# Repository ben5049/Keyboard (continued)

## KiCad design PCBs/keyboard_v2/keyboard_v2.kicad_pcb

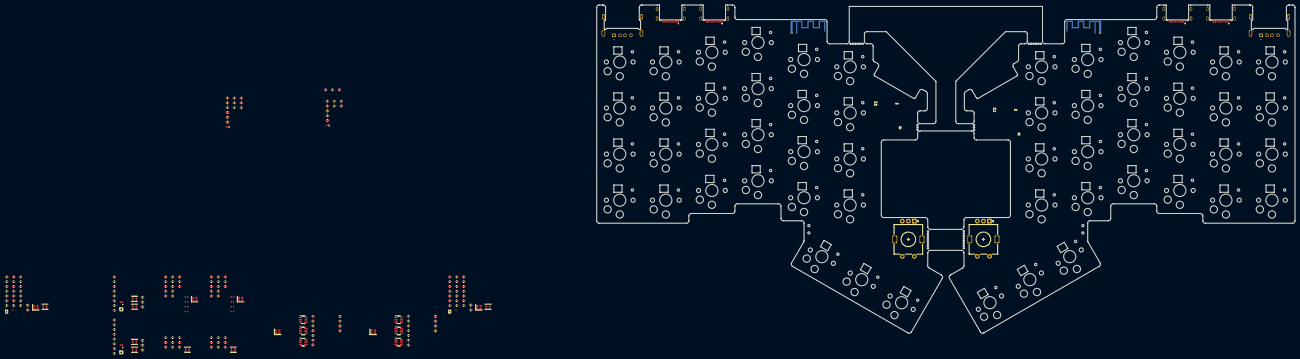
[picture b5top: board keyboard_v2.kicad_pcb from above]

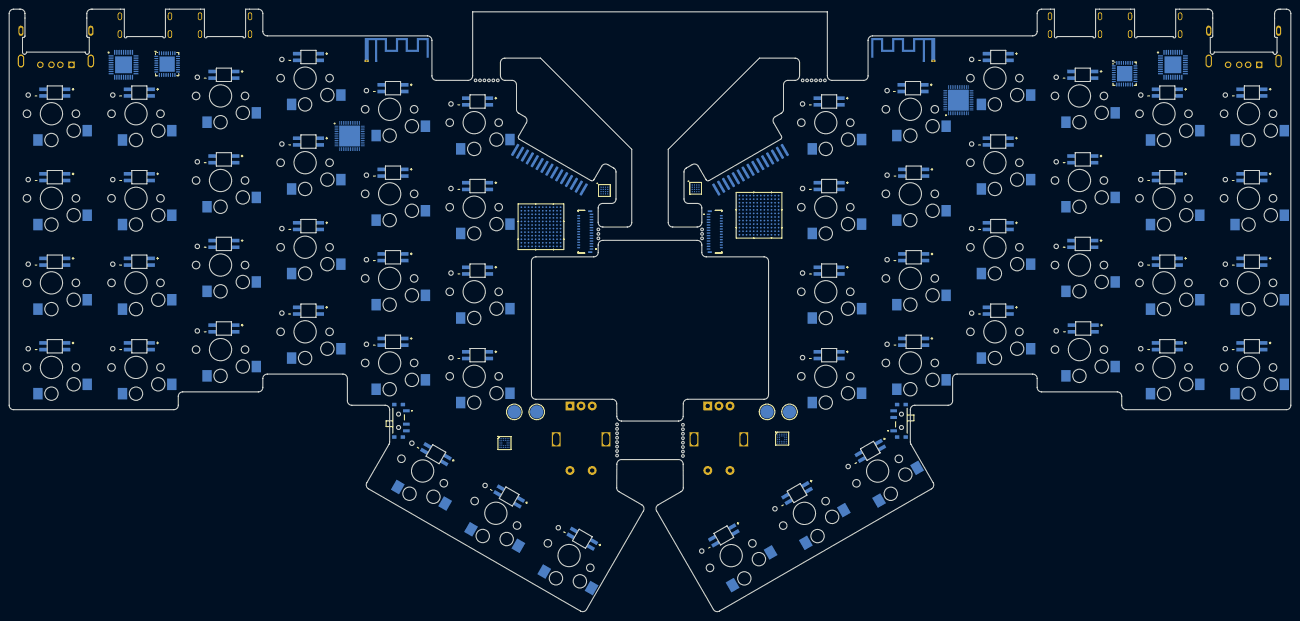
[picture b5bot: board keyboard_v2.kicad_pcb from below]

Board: 2 copper layers, 288.0 x 135.4 mm, 336 parts (78 on the bottom side), 197 nets, no tracks yet.

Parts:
AE202: Antenna_Shield; Texas_SWRA117D_2.4GHz_Left
AE302: Antenna_Shield; Texas_SWRA117D_2.4GHz_Right
C401, C404, C407, C503, C504, C505, C506, C507, C508, C808, C819, C1101, C1104, C1107, C1308, C1319, C1403, C1404, C1405, C1406, C1407, C1408: 10u; C_0402_1005Metric
C402, C405, C406, C602, C815, C1102, C1105, C1106, C1315, C1502: 4u7; C_0402_1005Metric
C403, C502, C606, C607, C812, C912, C915, C1012, C1015, C1103, C1312, C1402, C1506, C1507: 1u; C_0402_1005Metric
C408, C409, C1108, C1109: 22u; C_0402_1005Metric
C501, C821, C822, C1321, C1322, C1401: 2u2; C_0402_1005Metric
C601, C608, C701, C702, C703, C704, C705, C706, C707, C708, C709, C801, C802, C803, C804, C805, C806, C809, C810, C811, C813, C814, C816, C817, C907, C908, C909, C910, C911, C1007, C1008, C1009, C1010, C1011, C1201, C1202, C1203, C1204, C1205, C1206, C1207, C1208, C1209, C1301, C1302, C1303, C1304, C1305, C1306, C1309, C1310, C1311, C1313, C1314, C1316, C1317, C1501, C1508: 100n; C_0402_1005Metric
C604, C605, C1504, C1505: 10p; C_0402_1005Metric
C807, C1307: 1u; C_0201_0603Metric
C823, C824, C903, C904, C1003, C1004, C1323, C1324: 12p; C_0402_1005Metric
C905, C1005: 1p; C_0402_1005Metric
C906, C1006: 1p2; C_0402_1005Metric
C913, C1013: 100p; C_0402_1005Metric
C914, C1014: 47n; C_0402_1005Metric
D701, D702, D703, D704, D705, D706, D707, D708, D709, D710, D711, D712, D713, D714, D715, D716, D717, D718, D719, D720, D721, D722, D723, D724, D725, D726, D727, D1201, D1202, D1203, D1204, D1205, D1206, D1207, D1208, D1209, D1210, D1211, D1212, D1213, D1214, D1215, D1216, D1217, D1218, D1219, D1220, D1221, D1222, D1223, D1224, D1225, D1226, D1227: SK6812-E; LED_SK6812-E
IC501, IC1401: ADP5360ACBZ-2-R7; ADP5360ACBZ1R7
J201, J301: TMS-115-01-G-S; debug_header
J401, J1101: FH26W-27S-0.3SHW_60_; FH26W27S03SHW60
J601, J602, J1501, J1502: USB4510-03-1-A; USB4510031A
J603, J1503: GSB12J21C1EU; AMPHENOL_GSB12J21C1EU
L401, L801, L1101, L1301: 2u2; L_Murata_DFE201610P
L501, L502, L1401, L1402: 4u7; L_Murata_DFE201610P
L901, L1001: 10u; L_0402_1005Metric
L902, L1002: 4n7; L_0402_1005Metric
L905, L1005: 2n2; L_0402_1005Metric
L906, L1006: 15n; L_0402_1005Metric
Q501, Q1401: DMP2104LP-7; DMP2104LP7
Q701, Q1201: DMN21D2UFB-7B; DMN21D2UFB7B
R501, R606, R801, R802, R1301, R1302, R1401, R1506: 10k; R_0402_1005Metric
R502, R604, R708, R709, R1204, R1208, R1402, R1504: 100k; R_0402_1005Metric
R503, R1403: 50m; R_0402_1005Metric
R603, R1503: 47k; R_0402_1005Metric
R605, R1505: 12k; R_0402_1005Metric
R701, R1201: 4k7; R_0402_1005Metric
SW502, SW1402: PCM12SMTBR
SW701, SW1227: RIC11-31S15.5D7-TH; RotaryEncoder_Alps_EC11E-Switch_Vertical_H20mm
SW702, SW703, SW704, SW705, SW706, SW707, SW708, SW709, SW710, SW711, SW712, SW713, SW714, SW715, SW716, SW717, SW718, SW719, SW720, SW721, SW722, SW723, SW724, SW725, SW726, SW727, SW728, SW1201, SW1202, SW1203, SW1204, SW1205, SW1206, SW1207, SW1208, SW1209, SW1210, SW1211, SW1212, SW1213, SW1214, SW1215, SW1216, SW1217, SW1218, SW1219, SW1220, SW1221, SW1222, SW1223, SW1224, SW1225, SW1226, SW1228: SW_DIP_x01; choc-v1-hotswap
TP501, TP502, TP1401, TP1402: 3mm; TestPoint_Pad_D3.0mm
U401, U1101: 16B-WLCSP_2p34X2p43_RIT; RT4730WSC
U501, U1401: MAX9938TEBS+TG45; BGA4C50P2X2_100X100X67
U601, U602, U603, U1501, U1502, U1503: USBLC6-4SC6; SOT-23-6
U604, U1504: STM32G0B1KBUx; QFN-32-1EP_5x5mm_P0.5mm_EP3.45x3.45mm
U605, U1505: USB2533-1080AEN; QFN50P600X600X100-37N-D
U801, U1301: STM32U5G9ZJJ6Q; UFBGA144_STM
U802, U1302: M24256X-FCU6T_VF; BGA4C50P2X2_70X98X33
U901, U1001: nRF52840-QFAA-F-R7; QFN40P600X600X95-49N-D
Y601, Y1501: CX2016SA24000D0HLLG3; Crystal_SMD_2016-4Pin_2.0x1.6mm
Y802, Y902, Y1002, Y1302: 32MHz; Crystal_SMD_2016-4Pin_2.0x1.6mm

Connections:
+1V2: C606.1, C1506.1, U605.14 (VDDCR12), U1505.14 (VDDCR12)
+1V8: C506.1, C801.1, C802.1, C803.1, C804.1, C805.1, C806.1, C807.1, C808.1, C809.1, C810.1, C811.1, C813.1, C814.1, C819.1, C907.1, C908.1, C909.1, C910.1, C912.1, C1007.1, C1008.1, C1009.1, C1010.1, C1012.1, C1301.1, C1302.1, C1303.1, C1304.1, C1305.1, C1306.1, C1307.1, C1308.1, C1309.1, C1310.1, C1314.1, C1316.1, C1317.1, C1319.1, C1406.1, IC501.D1 (FB1), IC1401.D1 (FB1), J201.5, J201.15, J301.1, J301.11, J401.5, J401.17, J1101.5, J1101.17, L501.2, L1401.2, Q701.1 (G), Q1201.1 (G), R801.1, R802.1, R1301.1, R1302.1, U801.C2 (VBAT), U801.E3 (VDDDSI), U801.E8 (VDD), U801.E10 (VDD), U801.F5 (VDD), U801.G8 (VDD), U801.G10 (VDD), U801.H5 (VDD), U801.H7 (VDD), U801.J4 (VDDA), U801.J10 (VDD), U801.M8 (VDDSMPS), U802.A1 (VCC), U901.12 (VDD_1), U901.17 (VDD_2), U901.25 (VDD_3), U901.37 (VDD_4), U901.48 (VDD_5), U1001.12 (VDD_1), U1001.17 (VDD_2), U1001.25 (VDD_3), U1001.37 (VDD_4), U1001.48 (VDD_5), U1301.C2 (VBAT), U1301.E3 (VDDDSI), U1301.E8 (VDD), U1301.E10 (VDD), U1301.F5 (VDD), U1301.G8 (VDD), U1301.G10 (VDD), U1301.H5 (VDD), U1301.H7 (VDD), U1301.J4 (VDDA), U1301.J10 (VDD), U1301.M8 (VDDSMPS), U1302.A1 (VCC)
+3V3: C507.1, C601.1, C602.1, C607.1, C608.1, C815.1, C816.1, C817.1, C1311.1, C1313.1, C1315.1, C1407.1, C1501.1, C1502.1, C1507.1, C1508.1, IC501.A3 (VOUT2), IC1401.A3 (VOUT2), J201.10, J301.6, J401.23, J1101.23, U604.4 (VDD), U605.10 (VDDA33_1), U605.15 (VDD33_1), U605.23 (VDD33_2), U605.26 (RESET_N), U605.29 (VDDA33_2), U605.36 (VDDA33_3), U801.D10 (VDDUSB), U801.E6 (VDDIO2), U1301.D10 (VDDUSB), U1301.E6 (VDDIO2), U1504.4 (VDD), U1505.10 (VDDA33_1), U1505.15 (VDD33_1), U1505.23 (VDD33_2), U1505.26 (RESET_N), U1505.29 (VDDA33_2), U1505.36 (VDDA33_3)
+VBAT: C503.1, C1403.1, IC501.C6 (BSNS), IC501.D6 (ISOB), IC1401.C6 (BSNS), IC1401.D6 (ISOB), Q501.2 (D), Q1401.2 (D)
+VSYS: C401.1, C402.1, C505.1, C508.1, C1101.1, C1102.1, C1405.1, C1408.1, IC501.C1 (VIN2), IC501.D2 (VID1), IC501.E2 (EN1), IC501.F2 (VIN1), IC1401.C1 (VIN2), IC1401.D2 (VID1), IC1401.E2 (EN1), IC1401.F2 (VIN1), R503.2, R708.1, R709.1, R1204.1, R1208.1, R1403.2, U401.A1 (PVIN), U401.A2 (AVIN), U501.A2 (RS-), U1101.A1 (PVIN), U1101.A2 (AVIN), U1401.A2 (RS-)
/Left/Bluetooth/ANT: AE202.1 (A), C1006.1, L1005.2
/Left/Bluetooth/DCC1: L1001.1, U1001.47 (DCC)
/Left/Bluetooth/DCC2: L1001.2, L1006.1
/Left/Bluetooth/DEC1: C1011.1, U1001.1 (DEC1)
/Left/Bluetooth/DEC3: C1013.1, U1001.34 (DEC3)
/Left/Bluetooth/DEC4_6: C1014.1, C1015.1, L1006.2, U1001.33 (DEC6), U1001.46 (DEC4)
/Left/Bluetooth/RF1: L1002.1, U1001.31 (ANT)
/Left/Bluetooth/RF2: C1005.1, L1002.2, L1005.1
/Left/Bluetooth/RST: J201.11, U1001.16 (P0.18/NRESET)
/Left/Bluetooth/SWCLK: J201.13, U1001.27 (SWDCLK)
/Left/Bluetooth/SWDIO: J201.12, U1001.26 (SWDIO)
/Left/Bluetooth/XC1: C1003.2, U1001.35 (XC1), Y1002.3
/Left/Bluetooth/XC2: C1004.2, U1001.36 (XC2), Y1002.1
/Left/Display/AVDD: C1106.1, J1101.4, U1101.D2 (AVDD)
/Left/Display/C1N: C1103.2, U1101.B4 (C1N)
/Left/Display/C1P: C1103.1, U1101.A4 (C1P)
/Left/Display/DSI_CKN: J1101.11, U1301.F1 (DSI_CKN)
/Left/Display/DSI_CKP: J1101.10, U1301.F2 (DSI_CKP)
/Left/Display/DSI_D0N: J1101.8, U1301.E1 (DSI_D0N)
/Left/Display/DSI_D0P: J1101.7, U1301.E2 (DSI_D0P)
/Left/Display/DSI_TE: J1101.20, U1301.C5 (PB7)
/Left/Display/ELVDD: C1107.1, J1101.2, U1101.D3 (OVDD)
/Left/Display/ELVSS: C1108.1, C1109.1, J1101.1, U1101.D4 (OVSS)
/Left/Display/LX1: L1101.1, U1101.B1 (LX1)
/Left/Display/LX2: L1101.2, U1101.C1 (LX2)
/Left/Display/SWIRE: J1101.21, U1101.C3 (SWIRE)
/Left/Display/VON: C1105.1, U1101.C4 (VON)
/Left/Display/VOUT: C1104.1, U1101.D1 (VOUT)
/Left/Keys Left/ENC_A: R1204.2, SW1227.A
/Left/Keys Left/ENC_B: R1208.2, SW1227.B
/Left/Keys Left/LED1: D1201.4 (DIN), Q1201.3 (D), R1201.2
/Left/Keys Left/LED2: D1201.2 (DOUT), D1204.4 (DIN)
/Left/Keys Left/LED3: D1204.2 (DOUT), D1207.4 (DIN)
/Left/Keys Left/LED4: D1207.2 (DOUT), D1210.4 (DIN)
/Left/Keys Left/LED5: D1210.2 (DOUT), D1213.4 (DIN)
/Left/Keys Left/LED6: D1213.2 (DOUT), D1216.4 (DIN)
/Left/Keys Left/LED7: D1216.2 (DOUT), D1219.4 (DIN)
/Left/Keys Left/LED8: D1219.2 (DOUT), D1222.4 (DIN)
/Left/Keys Left/LED9: D1222.2 (DOUT), D1225.4 (DIN)
/Left/Keys Left/LED10: D1202.4 (DIN), D1225.2 (DOUT)
/Left/Keys Left/LED11: D1202.2 (DOUT), D1205.4 (DIN)
/Left/Keys Left/LED12: D1205.2 (DOUT), D1208.4 (DIN)
/Left/Keys Left/LED13: D1208.2 (DOUT), D1211.4 (DIN)
/Left/Keys Left/LED14: D1211.2 (DOUT), D1214.4 (DIN)
/Left/Keys Left/LED15: D1214.2 (DOUT), D1217.4 (DIN)
/Left/Keys Left/LED16: D1217.2 (DOUT), D1220.4 (DIN)
/Left/Keys Left/LED17: D1220.2 (DOUT), D1223.4 (DIN)
/Left/Keys Left/LED18: D1223.2 (DOUT), D1226.4 (DIN)
/Left/Keys Left/LED19: D1203.4 (DIN), D1226.2 (DOUT)
/Left/Keys Left/LED20: D1203.2 (DOUT), D1206.4 (DIN)
/Left/Keys Left/LED21: D1206.2 (DOUT), D1209.4 (DIN)
/Left/Keys Left/LED22: D1209.2 (DOUT), D1212.4 (DIN)
/Left/Keys Left/LED23: D1212.2 (DOUT), D1215.4 (DIN)
/Left/Keys Left/LED24: D1215.2 (DOUT), D1218.4 (DIN)
/Left/Keys Left/LED25: D1218.2 (DOUT), D1221.4 (DIN)
/Left/Keys Left/LED26: D1221.2 (DOUT), D1224.4 (DIN)
/Left/Keys Left/LED27: D1224.2 (DOUT), D1227.4 (DIN)
/Left/Main MCU Left/OSC_IN: C1323.2, U1301.H2 (PH0-OSC_IN), Y1302.3
/Left/Main MCU Left/OSC_OUT: C1324.2, U1301.J1 (PH1-OSC_OUT), Y1302.1
/Left/Main MCU Left/PWR_MR: IC1401.E4 (~MR), R1401.2
/Left/Main MCU Left/RST: J201.1, U1301.J2 (NRST)
/Left/Main MCU Left/SCL: R1302.2, U1302.A2 (SCL)
/Left/Main MCU Left/SDA: R1301.2, U1302.B1 (SDA)
/Left/Main MCU Left/SWCLK: J201.3, U1301.B11 (PA14)
/Left/Main MCU Left/SWDIO: J201.2, U1301.C10 (PA13)
/Left/Main MCU Left/USB_RST: J201.6, U1504.6 (PF2)
/Left/Main MCU Left/VDD11: C1321.1, C1322.1, L1301.1, U1301.D4 (VDD11), U1301.G3 (VDD11DSI), U1301.J9 (VDD11)
/Left/Main MCU Left/VLXSMPS: L1301.2, U1301.M7 (VLXSMPS)
/Left/Main MCU Left/VREF+: C1312.1, U1301.H3 (VREF+)
/Left/Power/BAT: Q1401.3 (S), SW1402.1 (A), TP1401.1
/Left/Power/BAT_SW: Q1401.1 (G), SW1402.2 (B)
/Left/Power/SWA_3V3: IC1401.B1 (SW2A), L1402.1
/Left/Power/SWB_3V3: IC1401.A2 (SW2B), L1402.2
/Left/Power/SW_1V8: IC1401.E1 (SW1), L1401.1
/Left/Power/THR: IC1401.B6 (THR), R1402.1
/Left/Power/VSYS_MON: C1404.1, IC1401.E6 (VSYS), R1403.1, U1401.A1 (RS+)
/Left/USB/CFG_SEL1: R1506.1, U1505.25 (HS_IND/~CFG_SEL1)
/Left/USB/RBIAS: R1505.1, U1505.35 (RBIAS)
/Left/USB/SWCLK: J201.8, U1504.25 (PA14)
/Left/USB/SWDIO: J201.7, U1504.24 (PA13)
/Left/USB/USB0_CC1: J1501.A5 (CC1), U1501.1 (I/O1), U1504.18 (PA8)
/Left/USB/USB0_CC2: J1501.B5 (CC2), U1501.3 (I/O2), U1504.17 (PB2)
/Left/USB/USB0_DN: J1501.A7 (D-), J1501.B7 (D-), U1501.6 (I/O4), U1505.30 (FLEX_USBUP_DM)
/Left/USB/USB0_DP: J1501.A6 (D+), J1501.B6 (D+), U1501.4 (I/O3), U1505.31 (FLEX_USBUP_DP)
/Left/USB/USB1_CC1: J1502.A5 (CC1), U1502.1 (I/O1), U1504.26 (PA15)
/Left/USB/USB1_CC2: J1502.B5 (CC2), U1502.3 (I/O2), U1504.28 (PB4)
/Left/USB/USB1_DN: J1502.A7 (D-), J1502.B7 (D-), U1502.6 (I/O4), U1505.1 (SWAP_USBDN1_DM/~PRT_DIS_M1)
/Left/USB/USB1_DP: J1502.A6 (D+), J1502.B6 (D+), U1502.4 (I/O3), U1505.2 (SWAP_USBDN1_DP/~PRT_DIS_P1)
/Left/USB/USB2_DN: J1503.2 (D-), U1503.1 (I/O1), U1505.3 (USBDN2_DM/~PRT_DIS_M2)
/Left/USB/USB2_DP: J1503.3 (D+), U1503.3 (I/O2), U1505.4 (USBDN2_DP/~PRT_DIS_P2)
/Left/USB/USB3_DN: U1301.C12 (PA11), U1505.6 (USBDN3_DM/~PRT_DIS_M3)
/Left/USB/USB3_DP: U1301.C11 (PA12), U1505.7 (USBDN3_DP/~PRT_DIS_P3)
/Left/USB/VBUS_DET: R1503.1, R1504.2, U1505.27 (VBUS_DET/PIO16)
/Left/USB/XTAL1: C1505.1, U1505.33 (XTAL1/REFCLK), Y1501.3
/Left/USB/XTAL2: C1504.1, U1505.32 (XTAL2), Y1501.1
/Right/Bluetooth/ANT: AE302.1 (A), C906.1, L905.2
/Right/Bluetooth/DCC1: L901.1, U901.47 (DCC)
/Right/Bluetooth/DCC2: L901.2, L906.1
/Right/Bluetooth/DEC1: C911.1, U901.1 (DEC1)
/Right/Bluetooth/DEC3: C913.1, U901.34 (DEC3)
/Right/Bluetooth/DEC4_6: C914.1, C915.1, L906.2, U901.33 (DEC6), U901.46 (DEC4)
/Right/Bluetooth/RF1: L902.1, U901.31 (ANT)
/Right/Bluetooth/RF2: C905.1, L902.2, L905.1
/Right/Bluetooth/RST: J301.5, U901.16 (P0.18/NRESET)
/Right/Bluetooth/SWCLK: J301.3, U901.27 (SWDCLK)
/Right/Bluetooth/SWDIO: J301.4, U901.26 (SWDIO)
/Right/Bluetooth/XC1: C903.2, U901.35 (XC1), Y902.3
/Right/Bluetooth/XC2: C904.2, U901.36 (XC2), Y902.1
/Right/Display/AVDD: C406.1, J401.4, U401.D2 (AVDD)
/Right/Display/C1N: C403.2, U401.B4 (C1N)
/Right/Display/C1P: C403.1, U401.A4 (C1P)
/Right/Display/DSI_CKN: J401.11, U801.F1 (DSI_CKN)
/Right/Display/DSI_CKP: J401.10, U801.F2 (DSI_CKP)
/Right/Display/DSI_D0N: J401.8, U801.E1 (DSI_D0N)
/Right/Display/DSI_D0P: J401.7, U801.E2 (DSI_D0P)
/Right/Display/DSI_TE: J401.20, U801.C5 (PB7)
/Right/Display/ELVDD: C407.1, J401.2, U401.D3 (OVDD)
/Right/Display/ELVSS: C408.1, C409.1, J401.1, U401.D4 (OVSS)
/Right/Display/LX1: L401.1, U401.B1 (LX1)
/Right/Display/LX2: L401.2, U401.C1 (LX2)
/Right/Display/SWIRE: J401.21, U401.C3 (SWIRE)
/Right/Display/VON: C405.1, U401.C4 (VON)
/Right/Display/VOUT: C404.1, U401.D1 (VOUT)
/Right/Keys Right/ENC_B: R709.2, SW701.A, SW701.B
/Right/Keys Right/LED1: D701.4 (DIN), Q701.3 (D), R701.2
/Right/Keys Right/LED2: D701.2 (DOUT), D704.4 (DIN)
/Right/Keys Right/LED3: D704.2 (DOUT), D707.4 (DIN)
/Right/Keys Right/LED4: D707.2 (DOUT), D710.4 (DIN)
/Right/Keys Right/LED5: D710.2 (DOUT), D713.4 (DIN)
/Right/Keys Right/LED6: D713.2 (DOUT), D716.4 (DIN)
/Right/Keys Right/LED7: D716.2 (DOUT), D719.4 (DIN)
/Right/Keys Right/LED8: D719.2 (DOUT), D722.4 (DIN)
/Right/Keys Right/LED9: D722.2 (DOUT), D725.4 (DIN)
/Right/Keys Right/LED10: D702.4 (DIN), D725.2 (DOUT)
/Right/Keys Right/LED11: D702.2 (DOUT), D705.4 (DIN)
/Right/Keys Right/LED12: D705.2 (DOUT), D708.4 (DIN)
/Right/Keys Right/LED13: D708.2 (DOUT), D711.4 (DIN)
/Right/Keys Right/LED14: D711.2 (DOUT), D714.4 (DIN)
/Right/Keys Right/LED15: D714.2 (DOUT), D717.4 (DIN)
/Right/Keys Right/LED16: D717.2 (DOUT), D720.4 (DIN)
/Right/Keys Right/LED17: D720.2 (DOUT), D723.4 (DIN)
/Right/Keys Right/LED18: D723.2 (DOUT), D726.4 (DIN)
/Right/Keys Right/LED19: D703.4 (DIN), D726.2 (DOUT)
/Right/Keys Right/LED20: D703.2 (DOUT), D706.4 (DIN)
/Right/Keys Right/LED21: D706.2 (DOUT), D709.4 (DIN)
/Right/Keys Right/LED22: D709.2 (DOUT), D712.4 (DIN)
/Right/Keys Right/LED23: D712.2 (DOUT), D715.4 (DIN)
/Right/Keys Right/LED24: D715.2 (DOUT), D718.4 (DIN)
/Right/Keys Right/LED25: D718.2 (DOUT), D721.4 (DIN)
/Right/Keys Right/LED26: D721.2 (DOUT), D724.4 (DIN)
/Right/Keys Right/LED27: D724.2 (DOUT), D727.4 (DIN)
/Right/Main MCU Right/OSC_IN: C823.2, U801.H2 (PH0-OSC_IN), Y802.3
/Right/Main MCU Right/OSC_OUT: C824.2, U801.J1 (PH1-OSC_OUT), Y802.1
/Right/Main MCU Right/PWR_MR: IC501.E4 (~MR), R501.2
/Right/Main MCU Right/RST: J301.15, U801.J2 (NRST)
/Right/Main MCU Right/SCL: R802.2, U802.A2 (SCL)
/Right/Main MCU Right/SDA: R801.2, U802.B1 (SDA)
/Right/Main MCU Right/SWCLK: J301.13, U801.B11 (PA14)
/Right/Main MCU Right/SWDIO: J301.14, U801.C10 (PA13)
/Right/Main MCU Right/USB_RST: J301.10, U604.6 (PF2)
/Right/Main MCU Right/VDD11: C821.1, C822.1, L801.1, U801.D4 (VDD11), U801.G3 (VDD11DSI), U801.J9 (VDD11)
/Right/Main MCU Right/VLXSMPS: L801.2, U801.M7 (VLXSMPS)
/Right/Main MCU Right/VREF+: C812.1, U801.H3 (VREF+)
/Right/Power/BAT: Q501.3 (S), SW502.1 (A), TP501.1
/Right/Power/BAT_SW: Q501.1 (G), SW502.2 (B)
/Right/Power/SWA_3V3: IC501.B1 (SW2A), L502.1
/Right/Power/SWB_3V3: IC501.A2 (SW2B), L502.2
/Right/Power/SW_1V8: IC501.E1 (SW1), L501.1
/Right/Power/THR: IC501.B6 (THR), R502.1
/Right/Power/VSYS_MON: C504.1, IC501.E6 (VSYS), R503.1, U501.A1 (RS+)
/Right/USB/CFG_SEL1: R606.1, U605.25 (HS_IND/~CFG_SEL1)
/Right/USB/RBIAS: R605.1, U605.35 (RBIAS)
/Right/USB/SWCLK: J301.8, U604.25 (PA14)
/Right/USB/SWDIO: J301.9, U604.24 (PA13)
/Right/USB/USB0_CC1: J601.A5 (CC1), U601.1 (I/O1), U604.18 (PA8)
/Right/USB/USB0_CC2: J601.B5 (CC2), U601.3 (I/O2), U604.17 (PB2)
/Right/USB/USB0_DN: J601.A7 (D-), J601.B7 (D-), U601.6 (I/O4), U605.30 (FLEX_USBUP_DM)
/Right/USB/USB0_DP: J601.A6 (D+), J601.B6 (D+), U601.4 (I/O3), U605.31 (FLEX_USBUP_DP)
/Right/USB/USB1_CC1: J602.A5 (CC1), U602.1 (I/O1), U604.26 (PA15)
/Right/USB/USB1_CC2: J602.B5 (CC2), U602.3 (I/O2), U604.28 (PB4)
/Right/USB/USB1_DN: J602.A7 (D-), J602.B7 (D-), U602.6 (I/O4), U605.1 (SWAP_USBDN1_DM/~PRT_DIS_M1)
/Right/USB/USB1_DP: J602.A6 (D+), J602.B6 (D+), U602.4 (I/O3), U605.2 (SWAP_USBDN1_DP/~PRT_DIS_P1)
/Right/USB/USB2_DN: J603.2 (D-), U603.1 (I/O1), U605.3 (USBDN2_DM/~PRT_DIS_M2)
/Right/USB/USB2_DP: J603.3 (D+), U603.3 (I/O2), U605.4 (USBDN2_DP/~PRT_DIS_P2)
/Right/USB/USB3_DN: U605.6 (USBDN3_DM/~PRT_DIS_M3), U801.C12 (PA11)
/Right/USB/USB3_DP: U605.7 (USBDN3_DP/~PRT_DIS_P3), U801.C11 (PA12)
/Right/USB/VBUS_DET: R603.1, R604.2, U605.27 (VBUS_DET/PIO16)
/Right/USB/XTAL1: C605.1, U605.33 (XTAL1/REFCLK), Y601.3
/Right/USB/XTAL2: C604.1, U605.32 (XTAL2), Y601.1
GND: AE202.2 (Shield), AE302.2 (Shield), C401.2, C402.2, C404.2, C405.2, C406.2, C407.2, C408.2, C409.2, C501.2, C502.2, C503.2, C504.2, C505.2, C506.2, C507.2, C508.2, C601.2, C602.2, C604.2, C605.2, C606.2, C607.2, C608.2, C701.2, C702.2, C703.2, C704.2, C705.2, C706.2, C707.2, C708.2, C709.2, C801.2, C802.2, C803.2, C804.2, C805.2, C806.2, C807.2, C808.2, C809.2, C810.2, C811.2, C812.2, C813.2, C814.2, C815.2, C816.2, C817.2, C819.2, C821.2, C822.2, C823.1, C824.1, C903.1, C904.1, C905.2, C906.2, C907.2, C908.2, C909.2, C910.2, C911.2, C912.2, C913.2, C914.2, C915.2, C1003.1, C1004.1, C1005.2, C1006.2, C1007.2, C1008.2, C1009.2, C1010.2, C1011.2, C1012.2, C1013.2, C1014.2, C1015.2, C1101.2, C1102.2, C1104.2, C1105.2, C1106.2, C1107.2, C1108.2, C1109.2, C1201.2, C1202.2, C1203.2, C1204.2, C1205.2, C1206.2, C1207.2, C1208.2, C1209.2, C1301.2, C1302.2, C1303.2, C1304.2, C1305.2, C1306.2, C1307.2, C1308.2, C1309.2, C1310.2, C1311.2, C1312.2, C1313.2, C1314.2, C1315.2, C1316.2, C1317.2, C1319.2, C1321.2, C1322.2, C1323.1, C1324.1, C1401.2, C1402.2, C1403.2, C1404.2, C1405.2, C1406.2, C1407.2, C1408.2, C1501.2, C1502.2, C1504.2, C1505.2, C1506.2, C1507.2, C1508.2, D701.3 (GND), D702.3 (GND), D703.3 (GND), D704.3 (GND), D705.3 (GND), D706.3 (GND), D707.3 (GND), D708.3 (GND), D709.3 (GND), D710.3 (GND), D711.3 (GND), D712.3 (GND), D713.3 (GND), D714.3 (GND), D715.3 (GND), D716.3 (GND), D717.3 (GND), D718.3 (GND), D719.3 (GND), D720.3 (GND), D721.3 (GND), D722.3 (GND), D723.3 (GND), D724.3 (GND), D725.3 (GND), D726.3 (GND), D727.3 (GND), D1201.3 (GND), D1202.3 (GND), D1203.3 (GND), D1204.3 (GND), D1205.3 (GND), D1206.3 (GND), D1207.3 (GND), D1208.3 (GND), D1209.3 (GND), D1210.3 (GND), D1211.3 (GND), D1212.3 (GND), D1213.3 (GND), D1214.3 (GND), D1215.3 (GND), D1216.3 (GND), D1217.3 (GND), D1218.3 (GND), D1219.3 (GND), D1220.3 (GND), D1221.3 (GND), D1222.3 (GND), D1223.3 (GND), D1224.3 (GND), D1225.3 (GND), D1226.3 (GND), D1227.3 (GND), IC501.A1 (PGND2), IC501.B2 (AGND2), IC501.B3 (ENSD), IC501.B4 (EN2), IC501.F1 (PGND1), IC501.F4 (AGND1), IC1401.A1 (PGND2), IC1401.B2 (AGND2), IC1401.B3 (ENSD), IC1401.B4 (EN2), IC1401.F1 (PGND1), IC1401.F4 (AGND1), J201.4, J201.9, J201.14, J301.2, J301.7, J301.12, J401.6, J401.9, J401.12, J401.14, J401.15, J401.18, J401.22, J401.MP1, J401.MP2, J601.A1 (GND), J601.A12 (GND), J601.MH1, J601.MH2, J601.MH3, J601.MH4, J602.A1 (GND), J602.A12 (GND), J602.MH1, J602.MH2, J602.MH3, J602.MH4, J603.4 (GND), J603.SH1 (SHIELD), J603.SH2 (SHIELD), J603.SH3 (SHIELD), J603.SH4 (SHIELD), J1101.6, J1101.9, J1101.12, J1101.14, J1101.15, J1101.18, J1101.22, J1101.MP1, J1101.MP2, J1501.A1 (GND), J1501.A12 (GND), J1501.MH1, J1501.MH2, J1501.MH3, J1501.MH4, J1502.A1 (GND), J1502.A12 (GND), J1502.MH1, J1502.MH2, J1502.MH3, J1502.MH4, J1503.4 (GND), J1503.SH1 (SHIELD), J1503.SH2 (SHIELD), J1503.SH3 (SHIELD), J1503.SH4 (SHIELD), R502.2, R604.1, R605.2, R606.2, R1402.2, R1504.1, R1505.2, R1506.2, SW502.3 (C), SW502.MP1, SW502.MP2, SW502.MP3, SW502.MP4, SW701.C, SW701.S2, SW702.1, SW703.1, SW704.1, SW705.1, SW706.1, SW707.1, SW708.1, SW709.1, SW710.1, SW711.1, SW712.1, SW713.1, SW714.1, SW715.1, SW716.1, SW717.1, SW718.1, SW719.1, SW720.1, SW721.1, SW722.1, SW723.1, SW724.1, SW725.1, SW726.1, SW727.1, SW728.1, SW1201.1, SW1202.1, SW1203.1, SW1204.1, SW1205.1, SW1206.1, SW1207.1, SW1208.1, SW1209.1, SW1210.1, SW1211.1, SW1212.1, SW1213.1, SW1214.1, SW1215.1, SW1216.1, SW1217.1, SW1218.1, SW1219.1, SW1220.1, SW1221.1, SW1222.1, SW1223.1, SW1224.1, SW1225.1, SW1226.1, SW1227.C, SW1227.S2, SW1228.1, SW1402.3 (C), SW1402.MP1, SW1402.MP2, SW1402.MP3, SW1402.MP4, TP502.1, TP1402.1, U401.A3 (AGND), U401.B2 (PGND), U401.B3 (CPGND), U501.B1 (GND), U601.2 (GND), U602.2 (GND), U603.2 (GND), U604.5 (VSS), U604.33 (VSS), U605.37 (VSS), U801.A1 (VSS), U801.A12 (VSS), U801.D1 (VSSDSI), U801.D5 (VSS), U801.D9 (VSS), U801.F3 (VSSDSI), U801.F6 (VSS), U801.F7 (VSS), U801.F10 (VSS), U801.G6 (VSS), U801.G7 (VSS), U801.H1 (VSSDSI), U801.H10 (VSS), U801.J3 (VSSA), U801.L8 (VSSSMPS), U801.M1 (VSS), U801.M12 (VSS), U802.B2 (VSS), U901.32 (VSS_PA), U901.45 (VSS_1), U901.49 (VSS_2), U1001.32 (VSS_PA), U1001.45 (VSS_1), U1001.49 (VSS_2), U1101.A3 (AGND), U1101.B2 (PGND), U1101.B3 (CPGND), U1301.A1 (VSS), U1301.A12 (VSS), U1301.D1 (VSSDSI), U1301.D5 (VSS), U1301.D9 (VSS), U1301.F3 (VSSDSI), U1301.F6 (VSS), U1301.F7 (VSS), U1301.F10 (VSS), U1301.G6 (VSS), U1301.G7 (VSS), U1301.H1 (VSSDSI), U1301.H10 (VSS), U1301.J3 (VSSA), U1301.L8 (VSSSMPS), U1301.M1 (VSS), U1301.M12 (VSS), U1302.B2 (VSS), U1401.B1 (GND), U1501.2 (GND), U1502.2 (GND), U1503.2 (GND), U1504.5 (VSS), U1504.33 (VSS), U1505.37 (VSS), Y601.2, Y601.4, Y802.2, Y802.4, Y902.2, Y902.4, Y1002.2, Y1002.4, Y1302.2, Y1302.4, Y1501.2, Y1501.4
VBUS: C501.1, C701.1, C702.1, C703.1, C704.1, C705.1, C706.1, C707.1, C708.1, C709.1, C1201.1, C1202.1, C1203.1, C1204.1, C1205.1, C1206.1, C1207.1, C1208.1, C1209.1, C1401.1, D701.1 (VDD), D702.1 (VDD), D703.1 (VDD), D704.1 (VDD), D705.1 (VDD), D706.1 (VDD), D707.1 (VDD), D708.1 (VDD), D709.1 (VDD), D710.1 (VDD), D711.1 (VDD), D712.1 (VDD), D713.1 (VDD), D714.1 (VDD), D715.1 (VDD), D716.1 (VDD), D717.1 (VDD), D718.1 (VDD), D719.1 (VDD), D720.1 (VDD), D721.1 (VDD), D722.1 (VDD), D723.1 (VDD), D724.1 (VDD), D725.1 (VDD), D726.1 (VDD), D727.1 (VDD), D1201.1 (VDD), D1202.1 (VDD), D1203.1 (VDD), D1204.1 (VDD), D1205.1 (VDD), D1206.1 (VDD), D1207.1 (VDD), D1208.1 (VDD), D1209.1 (VDD), D1210.1 (VDD), D1211.1 (VDD), D1212.1 (VDD), D1213.1 (VDD), D1214.1 (VDD), D1215.1 (VDD), D1216.1 (VDD), D1217.1 (VDD), D1218.1 (VDD), D1219.1 (VDD), D1220.1 (VDD), D1221.1 (VDD), D1222.1 (VDD), D1223.1 (VDD), D1224.1 (VDD), D1225.1 (VDD), D1226.1 (VDD), D1227.1 (VDD), IC501.F6 (VBUS), IC1401.F6 (VBUS), J601.A4 (VBUS), J601.A9 (VBUS), J602.A4 (VBUS), J602.A9 (VBUS), J603.1 (VCC), J1501.A4 (VBUS), J1501.A9 (VBUS), J1502.A4 (VBUS), J1502.A9 (VBUS), J1503.1 (VCC), R603.2, R701.1, R1201.1, R1503.2, U601.5 (VBUS), U602.5 (VBUS), U603.5 (VBUS), U1501.5 (VBUS), U1502.5 (VBUS), U1503.5 (VBUS)
VDD: C502.1, C1402.1, IC501.F5 (VDD), IC1401.F5 (VDD), R501.1, R1401.1

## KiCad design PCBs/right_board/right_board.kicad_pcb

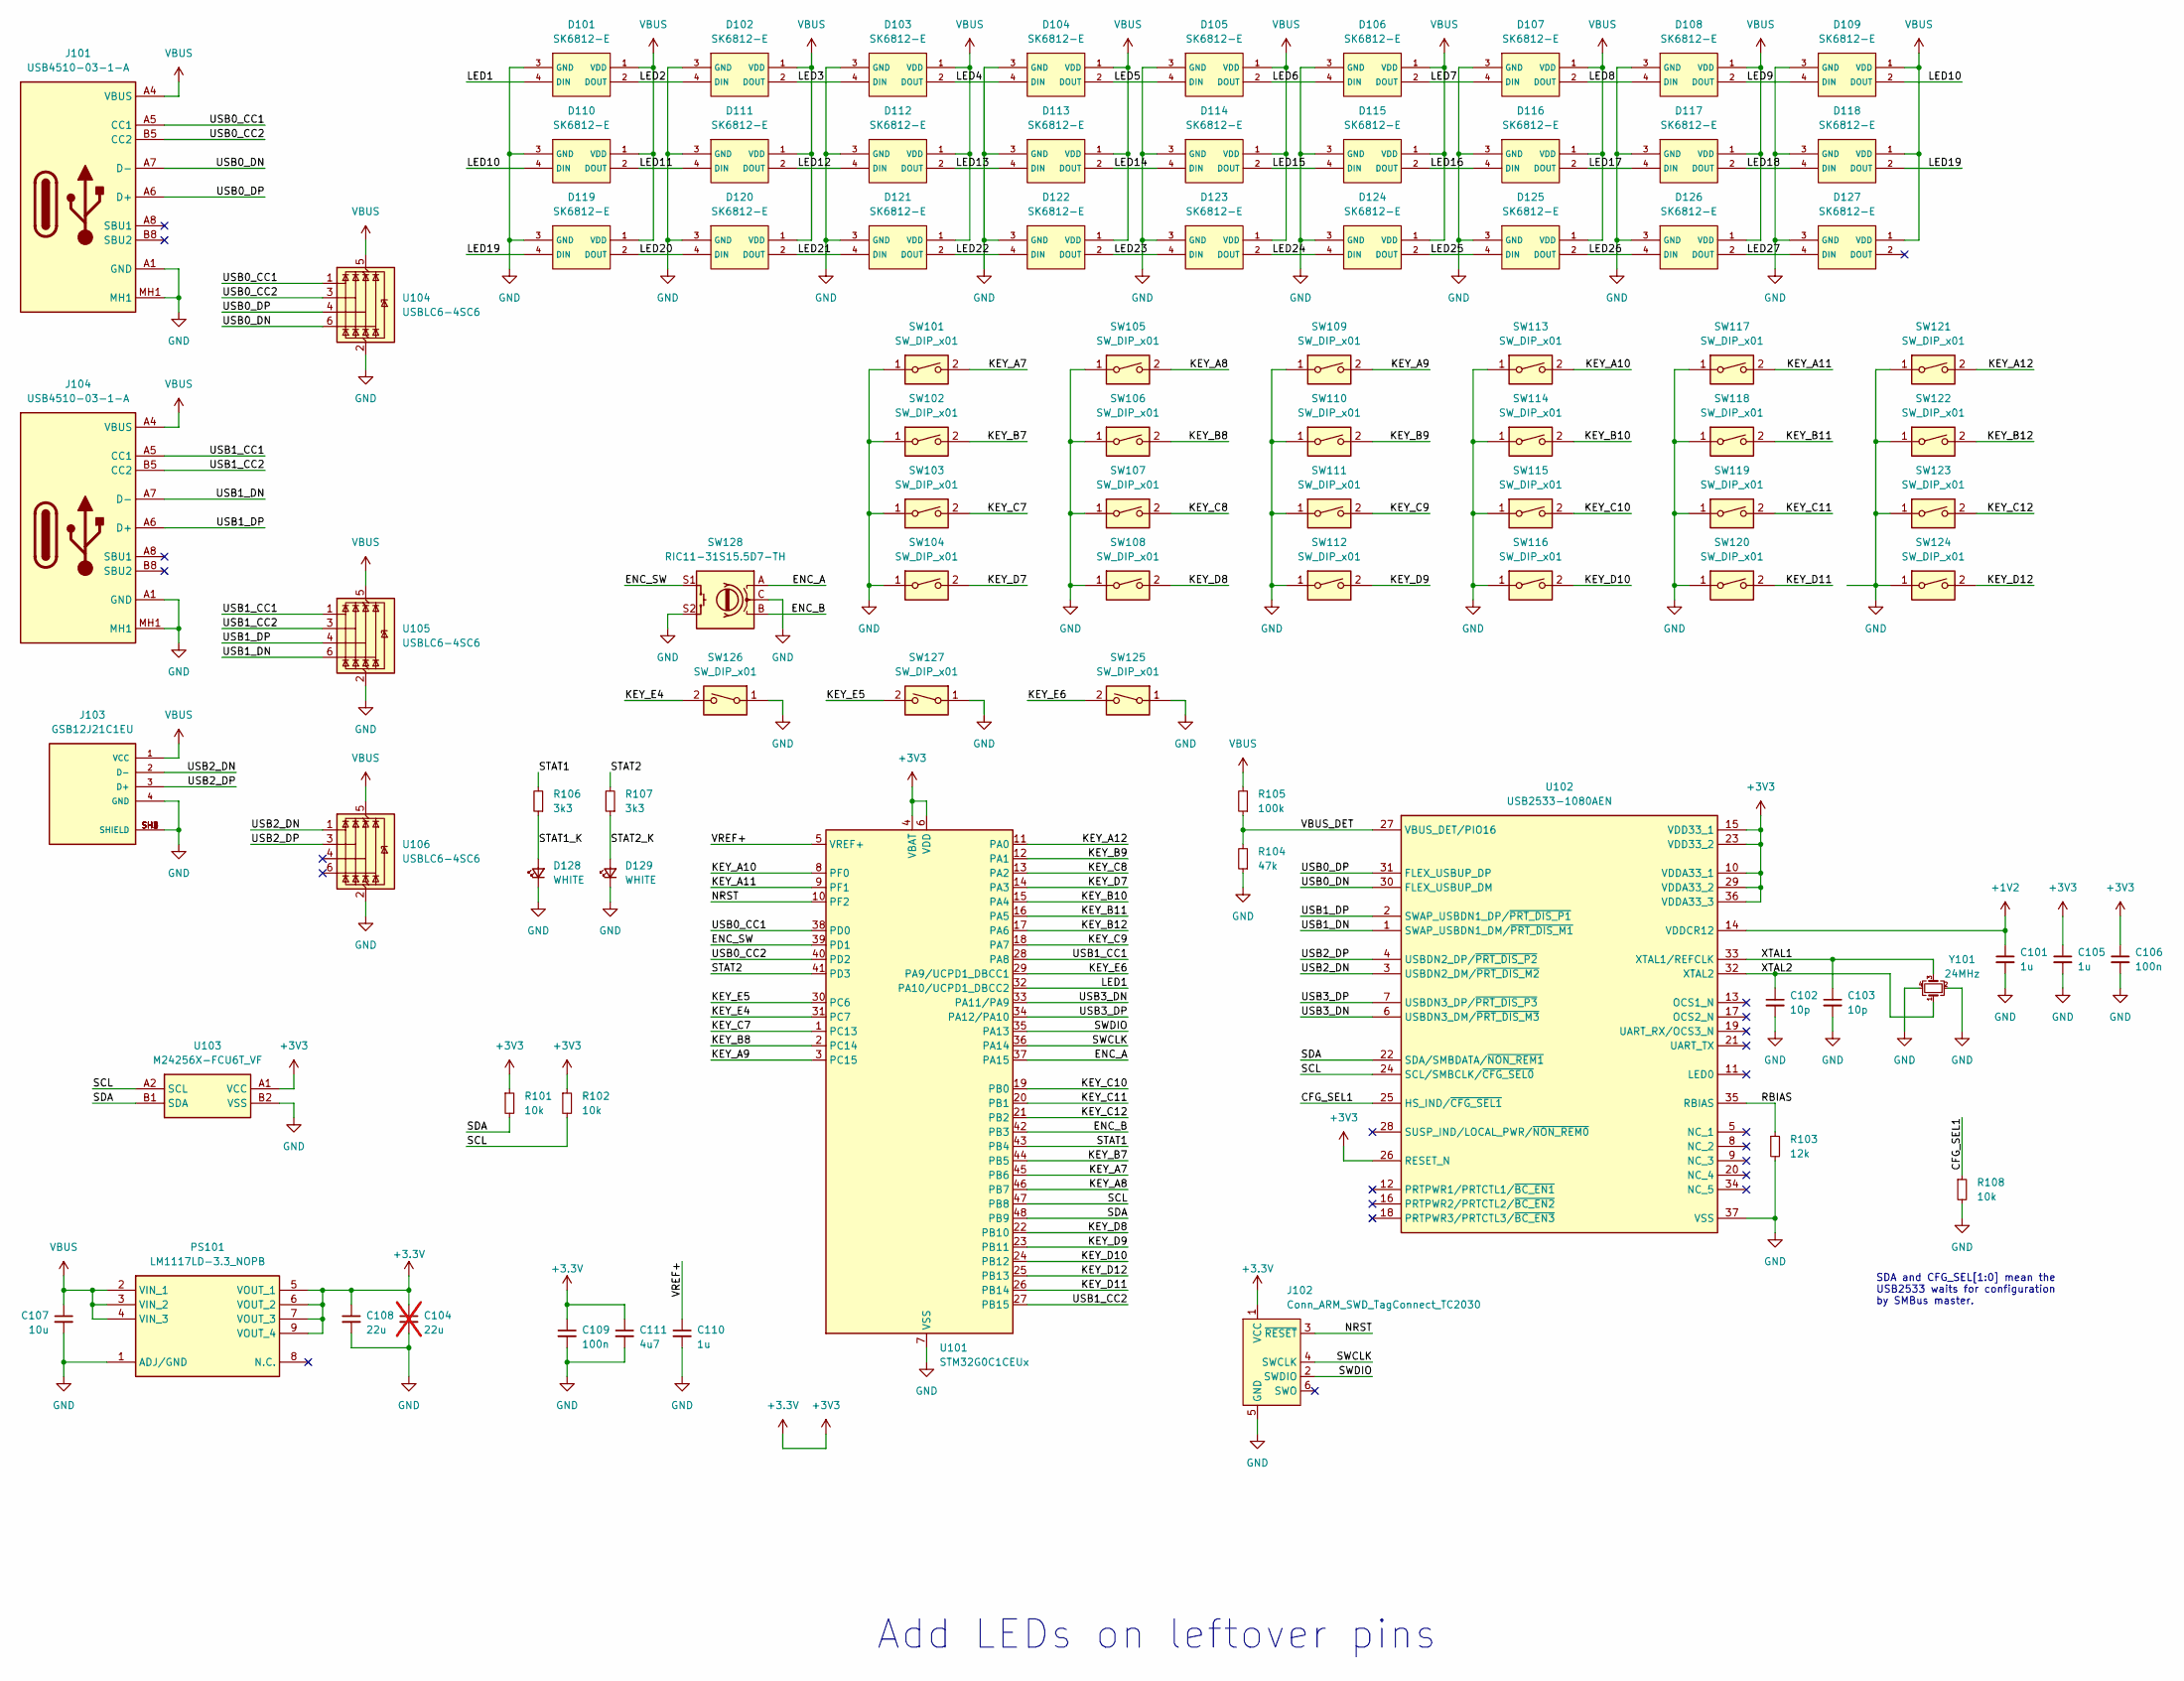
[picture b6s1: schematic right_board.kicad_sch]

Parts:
C101, C105, C110: 1u; C_0402_1005Metric
C102, C103: 10p; C_0402_1005Metric
C104: 22u; C_0603_1608Metric; not fitted
C106, C109: 100n; C_0402_1005Metric
C107: 10u; C_0603_1608Metric
C108: 22u; C_0603_1608Metric
C111: 4u7; C_0402_1005Metric
D101, D102, D103, D104, D105, D106, D107, D108, D109, D110, D111, D112, D113, D114, D115, D116, D117, D118, D119, D120, D121, D122, D123, D124, D125, D126, D127: SK6812-E; LED_SK6812-E; PARTREV 2
D128, D129: WHITE; LED_0402_1005Metric
J101, J104: USB4510-03-1-A; USB4510031A; Mouser Part Number 640-USB4510031A
J102: Conn_ARM_SWD_TagConnect_TC2030; Tag-Connect_TC2030-IDC-FP_2x03_P1.27mm_Vertical
J103: GSB12J21C1EU; AMPHENOL_GSB12J21C1EU; PARTREV B
PS101: LM1117LD-3.3_NOPB; LP2989AILD33NOPB; Mouser Part Number 926-LM1117LD33NOPB
R101, R102, R108: 10k; R_0402_1005Metric
R103: 12k; R_0402_1005Metric
R104: 47k; R_0402_1005Metric
R105: 100k; R_0402_1005Metric
R106, R107: 3k3; R_0402_1005Metric
SW101, SW102, SW103, SW104, SW105, SW106, SW107, SW108, SW109, SW110, SW111, SW112, SW113, SW114, SW115, SW116, SW117, SW118, SW119, SW120, SW121, SW122, SW123, SW124, SW125, SW126, SW127: SW_DIP_x01; gateron-ks27-hotswap
SW128: RIC11-31S15.5D7-TH; RotaryEncoder_Alps_EC11E-Switch_Vertical_H20mm
U101: STM32G0C1CEUx; QFN-48-1EP_7x7mm_P0.5mm_EP5.6x5.6mm
U102: USB2533-1080AEN; QFN50P600X600X100-37N-D; Mouser Part Number 579-USB2533-1080AEN
U103: M24256X-FCU6T_VF; BGA4C50P2X2_100X100X67; Mouser Part Number 511-M24256X-FCU6T/VF
U104, U105, U106: USBLC6-4SC6; SOT-23-6
Y101: CX2016SA24000D0HLLG3; Crystal_SMD_2016-4Pin_2.0x1.6mm

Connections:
+1V2: C101.1, U102.14 (VDDCR12)
+3.3V: C104.1, C105.1, C106.1, C108.1, C109.1, C111.1, J102.1 (VCC), PS101.5 (VOUT_1), PS101.6 (VOUT_2), PS101.7 (VOUT_3), PS101.9 (VOUT_4), R101.1, R102.1, U101.4 (VBAT), U101.6 (VDD), U102.10 (VDDA33_1), U102.15 (VDD33_1), U102.23 (VDD33_2), U102.26 (RESET_N), U102.29 (VDDA33_2), U102.36 (VDDA33_3), U103.A1 (VCC)
/CFG_SEL1: R108.1, U102.25 (HS_IND/~CFG_SEL1)
/ENC_A: SW128.A, U101.37 (PA15)
/ENC_B: SW128.B, U101.42 (PB3)
/ENC_SW: SW128.S1, U101.39 (PD1)
/KEY_A7: SW101.2, U101.45 (PB6)
/KEY_A8: SW105.2, U101.46 (PB7)
/KEY_A9: SW109.2, U101.3 (PC15)
/KEY_A10: SW113.2, U101.8 (PF0)
/KEY_A11: SW117.2, U101.9 (PF1)
/KEY_A12: SW121.2, U101.11 (PA0)
/KEY_B7: SW102.2, U101.44 (PB5)
/KEY_B8: SW106.2, U101.2 (PC14)
/KEY_B9: SW110.2, U101.12 (PA1)
/KEY_B10: SW114.2, U101.15 (PA4)
/KEY_B11: SW118.2, U101.16 (PA5)
/KEY_B12: SW122.2, U101.17 (PA6)
/KEY_C7: SW103.2, U101.1 (PC13)
/KEY_C8: SW107.2, U101.13 (PA2)
/KEY_C9: SW111.2, U101.18 (PA7)
/KEY_C10: SW115.2, U101.19 (PB0)
/KEY_C11: SW119.2, U101.20 (PB1)
/KEY_C12: SW123.2, U101.21 (PB2)
/KEY_D7: SW104.2, U101.14 (PA3)
/KEY_D8: SW108.2, U101.22 (PB10)
/KEY_D9: SW112.2, U101.23 (PB11)
/KEY_D10: SW116.2, U101.24 (PB12)
/KEY_D11: SW120.2, U101.26 (PB14)
/KEY_D12: SW124.2, U101.25 (PB13)
/KEY_E4: SW126.2, U101.31 (PC7)
/KEY_E5: SW127.2, U101.30 (PC6)
/KEY_E6: SW125.2, U101.29 (PA9/UCPD1_DBCC1)
/LED1: D101.4 (DIN), U101.32 (PA10/UCPD1_DBCC2)
/LED2: D101.2 (DOUT), D102.4 (DIN)
/LED3: D102.2 (DOUT), D103.4 (DIN)
/LED4: D103.2 (DOUT), D104.4 (DIN)
/LED5: D104.2 (DOUT), D105.4 (DIN)
/LED6: D105.2 (DOUT), D106.4 (DIN)
/LED7: D106.2 (DOUT), D107.4 (DIN)
/LED8: D107.2 (DOUT), D108.4 (DIN)
/LED9: D108.2 (DOUT), D109.4 (DIN)
/LED10: D109.2 (DOUT), D110.4 (DIN)
/LED11: D110.2 (DOUT), D111.4 (DIN)
/LED12: D111.2 (DOUT), D112.4 (DIN)
/LED13: D112.2 (DOUT), D113.4 (DIN)
/LED14: D113.2 (DOUT), D114.4 (DIN)
/LED15: D114.2 (DOUT), D115.4 (DIN)
/LED16: D115.2 (DOUT), D116.4 (DIN)
/LED17: D116.2 (DOUT), D117.4 (DIN)
/LED18: D117.2 (DOUT), D118.4 (DIN)
/LED19: D118.2 (DOUT), D119.4 (DIN)
/LED20: D119.2 (DOUT), D120.4 (DIN)
/LED21: D120.2 (DOUT), D121.4 (DIN)
/LED22: D121.2 (DOUT), D122.4 (DIN)
/LED23: D122.2 (DOUT), D123.4 (DIN)
/LED24: D123.2 (DOUT), D124.4 (DIN)
/LED25: D124.2 (DOUT), D125.4 (DIN)
/LED26: D125.2 (DOUT), D126.4 (DIN)
/LED27: D126.2 (DOUT), D127.4 (DIN)
/NRST: J102.3 (~RESET), U101.10 (PF2)
/RBIAS: R103.1, U102.35 (RBIAS)
/SCL: R102.2, U101.47 (PB8), U102.24 (SCL/SMBCLK/~CFG_SEL0), U103.A2 (SCL)
/SDA: R101.2, U101.48 (PB9), U102.22 (SDA/SMBDATA/~NON_REM1), U103.B1 (SDA)
/STAT1: R106.2, U101.43 (PB4)
/STAT1_K: D128.2 (A), R106.1
/STAT2: R107.2, U101.41 (PD3)
/STAT2_K: D129.2 (A), R107.1
/SWCLK: J102.4 (SWCLK), U101.36 (PA14)
/SWDIO: J102.2 (SWDIO), U101.35 (PA13)
/USB0_CC1: J101.A5 (CC1), U101.38 (PD0), U104.1 (I/O1)
/USB0_CC2: J101.B5 (CC2), U101.40 (PD2), U104.3 (I/O2)
/USB0_DN: J101.A7 (D-), J101.B7 (D-), U102.30 (FLEX_USBUP_DM), U104.6 (I/O4)
/USB0_DP: J101.A6 (D+), J101.B6 (D+), U102.31 (FLEX_USBUP_DP), U104.4 (I/O3)
/USB1_CC1: J104.A5 (CC1), U101.28 (PA8), U105.1 (I/O1)
/USB1_CC2: J104.B5 (CC2), U101.27 (PB15), U105.3 (I/O2)
/USB1_DN: J104.A7 (D-), J104.B7 (D-), U102.1 (SWAP_USBDN1_DM/~PRT_DIS_M1), U105.6 (I/O4)
/USB1_DP: J104.A6 (D+), J104.B6 (D+), U102.2 (SWAP_USBDN1_DP/~PRT_DIS_P1), U105.4 (I/O3)
/USB2_DN: J103.2 (D-), U102.3 (USBDN2_DM/~PRT_DIS_M2), U106.1 (I/O1)
/USB2_DP: J103.3 (D+), U102.4 (USBDN2_DP/~PRT_DIS_P2), U106.3 (I/O2)
/USB3_DN: U101.33 (PA11/PA9), U102.6 (USBDN3_DM/~PRT_DIS_M3)
/USB3_DP: U101.34 (PA12/PA10), U102.7 (USBDN3_DP/~PRT_DIS_P3)
/VBUS_DET: R104.2, R105.1, U102.27 (VBUS_DET/PIO16)
/VREF+: C110.1, U101.5 (VREF+)
/XTAL1: C103.1, U102.33 (XTAL1/REFCLK), Y101.3
/XTAL2: C102.1, U102.32 (XTAL2), Y101.1
GND: C101.2, C102.2, C103.2, C104.2, C105.2, C106.2, C107.2, C108.2, C109.2, C110.2, C111.2, D101.3 (GND), D102.3 (GND), D103.3 (GND), D104.3 (GND), D105.3 (GND), D106.3 (GND), D107.3 (GND), D108.3 (GND), D109.3 (GND), D110.3 (GND), D111.3 (GND), D112.3 (GND), D113.3 (GND), D114.3 (GND), D115.3 (GND), D116.3 (GND), D117.3 (GND), D118.3 (GND), D119.3 (GND), D120.3 (GND), D121.3 (GND), D122.3 (GND), D123.3 (GND), D124.3 (GND), D125.3 (GND), D126.3 (GND), D127.3 (GND), D128.1 (K), D129.1 (K), J101.A1 (GND), J101.A12 (GND), J101.MH1, J101.MH2, J101.MH3, J101.MH4, J102.5 (GND), J103.4 (GND), J103.SH1 (SHIELD), J103.SH2 (SHIELD), J103.SH3 (SHIELD), J103.SH4 (SHIELD), J104.A1 (GND), J104.A12 (GND), J104.MH1, J104.MH2, J104.MH3, J104.MH4, PS101.1 (ADJ/GND), R103.2, R104.1, R108.2, SW101.1, SW102.1, SW103.1, SW104.1, SW105.1, SW106.1, SW107.1, SW108.1, SW109.1, SW110.1, SW111.1, SW112.1, SW113.1, SW114.1, SW115.1, SW116.1, SW117.1, SW118.1, SW119.1, SW120.1, SW121.1, SW122.1, SW123.1, SW124.1, SW125.1, SW126.1, SW127.1, SW128.C, SW128.S2, U101.7 (VSS), U101.49 (VSS), U102.37 (VSS), U103.B2 (VSS), U104.2 (GND), U105.2 (GND), U106.2 (GND), Y101.2, Y101.4
VBUS: C107.1, D101.1 (VDD), D102.1 (VDD), D103.1 (VDD), D104.1 (VDD), D105.1 (VDD), D106.1 (VDD), D107.1 (VDD), D108.1 (VDD), D109.1 (VDD), D110.1 (VDD), D111.1 (VDD), D112.1 (VDD), D113.1 (VDD), D114.1 (VDD), D115.1 (VDD), D116.1 (VDD), D117.1 (VDD), D118.1 (VDD), D119.1 (VDD), D120.1 (VDD), D121.1 (VDD), D122.1 (VDD), D123.1 (VDD), D124.1 (VDD), D125.1 (VDD), D126.1 (VDD), D127.1 (VDD), J101.A4 (VBUS), J101.A9 (VBUS), J103.1 (VCC), J104.A4 (VBUS), J104.A9 (VBUS), PS101.2 (VIN_1), PS101.3 (VIN_2), PS101.4 (VIN_3), R105.2, U104.5 (VBUS), U105.5 (VBUS), U106.5 (VBUS)

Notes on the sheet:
SDA and CFG_SEL[1:0] mean the USB2533 waits for configuration by SMBus master.
Add LEDs on leftover pins
